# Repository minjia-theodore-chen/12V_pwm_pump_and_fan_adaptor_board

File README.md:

# 12V PWM Pump and Fan Adaptor Board

This project uses a self-contained, project-specific library structure to ensure maximum portability across different machines via Git.

## KiCad Library Organization

Instead of relying on global or system-wide KiCad libraries, all components (symbols, footprints, and 3D models) are stored locally within the `lib/` directory.

### Directory Structure

The `lib/` directory is organized as follows:

*   **`lib/downloads/`**: Staging area for raw files downloaded from component vendors (e.g., `.zip` files containing symbols, footprints, and 3D models).
*   **`lib/symbols/`**: Contains the project's schematic symbol libraries (`.kicad_sym`).
*   **`lib/footprints/`**: Contains the project's footprint libraries (`.pretty` folders with `.kicad_mod` files).
*   **`lib/3D/`**: Stores the 3D models (e.g., `.stp` files) used by the footprints.

Within these directories, files are typically categorized by component type (e.g., `connectors`).

### Linking Assets

To ensure portability, all assets are linked using the project-relative path variable `${KIPRJMOD}`:

1.  **Library Tables**: In the `fp-lib-table` (and `sym-lib-table`), libraries are referenced relatively, e.g., `${KIPRJMOD}/lib/footprints/connectors/connectors.pretty`.
2.  **Footprint to 3D Model**: In the footprint editor, the 3D model is linked using the relative path, e.g., `${KIPRJMOD}/lib/3D/connectors/0039300080.stp`.
3.  **Symbol to Footprint**: Symbols in the schematic are linked to the local footprint library, e.g., `connectors:39-30-Y080`.

## Workflow for Adding New Components

When adding a new component from the web, follow this routine:

1.  **Download**: Save the downloaded KiCad library archive into `lib/downloads/`.
2.  **Decompress & Organize**: Extract the files and move them to their respective directories (`.kicad_sym` to `lib/symbols/`, `.kicad_mod` to `lib/footprints/`, and `.stp`/`.wrl` to `lib/3D/`). Create new library files/folders if necessary.
3.  **Link 3D Model**: Open the footprint in the KiCad Footprint Editor, configure the 3D model path to point to the correct file in `lib/3D/` using the `${KIPRJMOD}` prefix, and save it to the correct project footprint library.
4.  **Link Footprint**: Open the symbol in the KiCad Symbol Editor (or directly in the schematic), update the Footprint property to point to the newly imported footprint in the local library, and save it.

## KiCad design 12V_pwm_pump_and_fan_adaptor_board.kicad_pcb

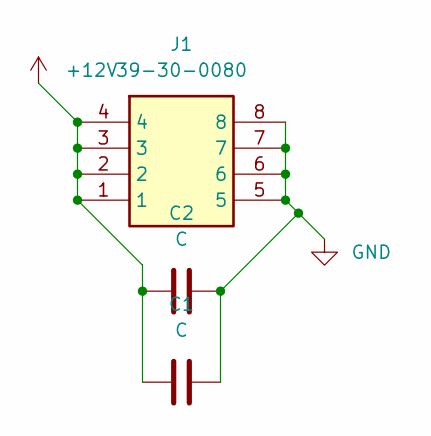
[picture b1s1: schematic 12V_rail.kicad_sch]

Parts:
C1, C2: C
J1: 39-30-0080; 39-30-Y080; Manufacturer_Part_Number 39-30-0080; Mouser Part Number 538-39-30-0080

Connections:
+12V: C1.1, C2.1, J1.1, J1.2, J1.3, J1.4; also elsewhere on the board
GND: C1.2, C2.2, J1.5, J1.6, J1.7, J1.8; also elsewhere on the board

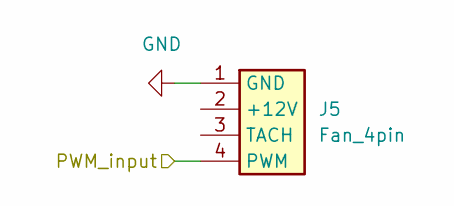
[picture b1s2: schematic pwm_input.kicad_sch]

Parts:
J5: Fan_4pin; CONN_SD-47053-001_H10p00_MOL

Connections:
/output_connectors/shared_pwm_signal: J5.4 (PWM); also elsewhere on the board
GND: J5.1 (GND); also elsewhere on the board

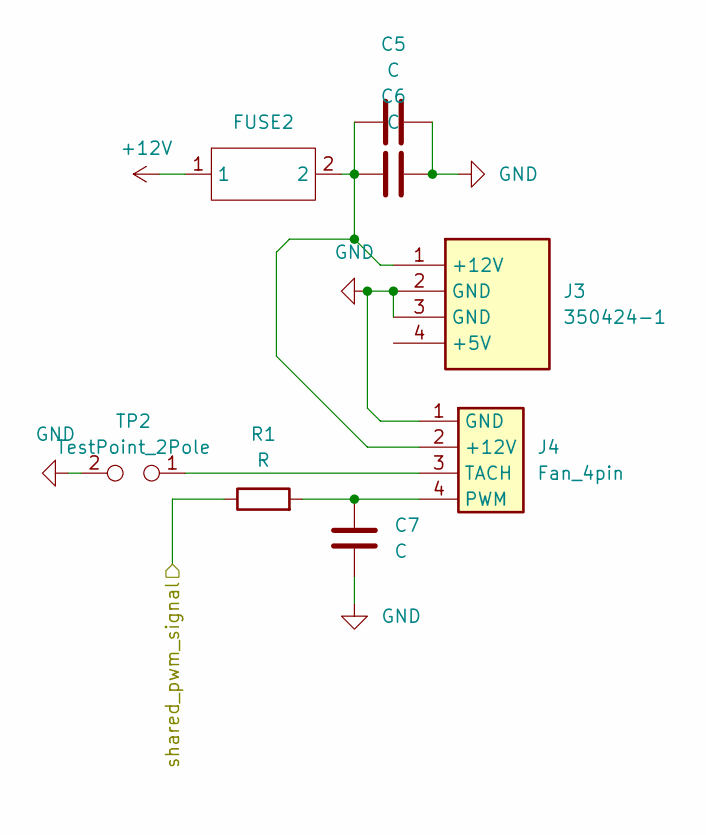
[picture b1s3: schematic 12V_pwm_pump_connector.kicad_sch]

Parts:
C5, C6, C7: C
FUSE2: SMD2920P500TF16
J3: 350424-1; Manufacturer_Part_Number 350424-1; Mouser Part Number 571-3504241
J4: Fan_4pin; CONN_SD-47053-001_H10p00_MOL
R1: R
TP2: TestPoint_2Pole

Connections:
+12V: FUSE2.1; also elsewhere on the board
/output_connectors/shared_pwm_signal: R1.1; also elsewhere on the board
GND: C5.2, C6.2, C7.2, J3.2 (GND), J3.3 (GND), J4.1 (GND), TP2.2; also elsewhere on the board
unnamed: C5.1, C6.1, FUSE2.2, J3.1 (+12V), J4.2 (+12V)
unnamed: C7.1, J4.4 (PWM), R1.2
unnamed: J4.3 (TACH), TP2.1

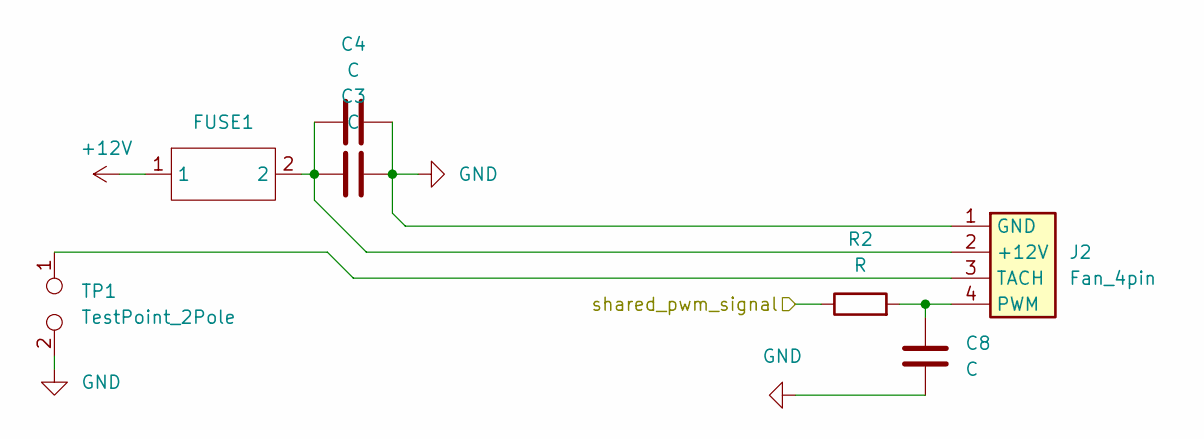
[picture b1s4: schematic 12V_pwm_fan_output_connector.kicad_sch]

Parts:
C3, C4, C8: C
FUSE1: SMD2920P500TF16
J2: Fan_4pin; CONN_SD-47053-001_H10p00_MOL
R2: R
TP1: TestPoint_2Pole

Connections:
+12V: FUSE1.1; also elsewhere on the board
/output_connectors/shared_pwm_signal: R2.1; also elsewhere on the board
GND: C3.2, C4.2, C8.2, J2.1 (GND), TP1.2; also elsewhere on the board
unnamed: C3.1, C4.1, FUSE1.2, J2.2 (+12V)
unnamed: C8.1, J2.4 (PWM), R2.2
unnamed: J2.3 (TACH), TP1.1

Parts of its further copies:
C9, C10, C11, C12, C13, C14: C
J6, J7: Fan_4pin; CONN_SD-47053-001_H10p00_MOL
R3, R4: R
TP3, TP4: TestPoint_2Pole

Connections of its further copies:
/output_connectors/shared_pwm_signal: R3.1, R4.1; also elsewhere on the board
GND: C9.2, C10.2, C11.2, C12.2, C13.2, C14.2, J6.1 (GND), J7.1 (GND), TP3.2, TP4.2; also elsewhere on the board
unnamed 9: C9.1, C10.1, J6.2 (+12V); also elsewhere on the board
unnamed: C11.1, J6.4 (PWM), R3.2
unnamed: J6.3 (TACH), TP3.1
unnamed 12: C12.1, C13.1, J7.2 (+12V); also elsewhere on the board
unnamed: C14.1, J7.4 (PWM), R4.2
unnamed: J7.3 (TACH), TP4.1

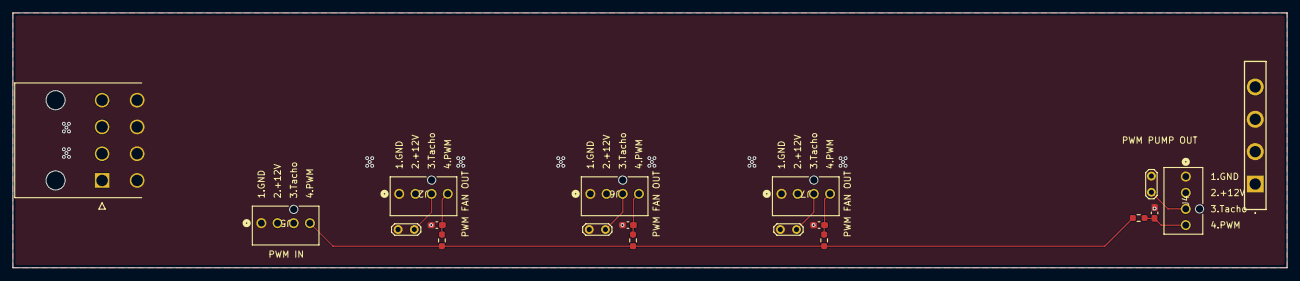
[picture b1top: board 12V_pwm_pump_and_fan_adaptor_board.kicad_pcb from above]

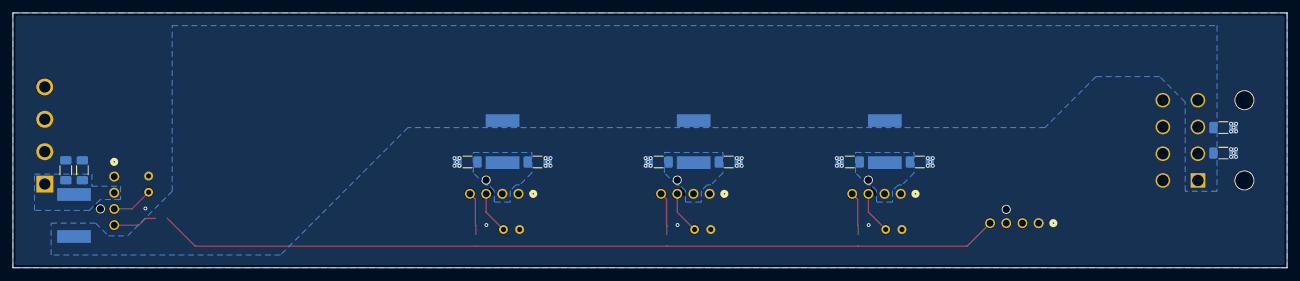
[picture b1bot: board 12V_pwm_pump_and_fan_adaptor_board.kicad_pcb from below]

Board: 4 copper layers, 200.0 x 40.0 mm, 33 parts (14 on the bottom side), 15 nets.

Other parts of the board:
FUSE3, FUSE4: SMD2920P500TF16

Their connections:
+12V: FUSE3.1, FUSE4.1; also elsewhere on the board
unnamed 9: FUSE3.2; also elsewhere on the board
unnamed 12: FUSE4.2; also elsewhere on the board
